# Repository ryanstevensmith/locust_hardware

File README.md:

# Locust Hardware

Open hardware for **Locust**, a low-cost acoustic monitoring sensor developed with Imperial College London. It records audio to a microSD card in the field and can optionally send data over NB-IoT through a plug-in daughter board.

This repository contains the KiCad design files, manufacturing outputs and a firmware flashing tool for the electronics.

## Boards

| Board | Description | Latest release |
|-------|-------------|----------------|
| [IC_001 - Low Cost Audio Sensor](IC_001%20-%20Low%20Cost%20Audio%20Sensor/) | Main board: ESP32-S3 audio recorder with microSD storage and Li-ion battery management | v3.0 |
| [IC_002 - Acoustic Nb-IoT Daughter Board](IC_002%20-%20Acoustic%20Nb-IoT%20Daughter%20Board/) | Optional NB-IoT add-on board for sending data off the device | v3.0 |

### IC_001 – Low Cost Audio Sensor

- **MCU:** Espressif ESP32-S3-WROOM-1 (N16R8: 16 MB flash, 8 MB PSRAM)
- **Audio chain:** Syntiant SPV0142LR5H analogue MEMS microphone → TI OPA1671 preamp → TI TLV320ADC3101 audio ADC (I2S)
- **Storage:** microSD card
- **Power:** single-cell Li-ion input, TI BQ21080 charger, TI BQ27427 fuel gauge, 2× TI TPS63000 buck-boost regulators, USB-C for charging and programming
- **User interface:** 5 buttons and an addressable RGB LED panel for setting the clock, sample rate (8–96 kHz), duty cycle, gain and recording schedule, plus status LEDs
- **Expansion:** 2× Qwiic/STEMMA QT (JST-SH, I2C) and a 10-way FFC connector (J6) to IC_002

### IC_002 – Acoustic NB-IoT Daughter Board

- **Modem:** Quectel BC65 NB-IoT module
- **SIM:** nano-SIM holder with ESD protection
- **Antenna:** edge-mount SMA or U.FL (fit **one** antenna at a time)
- **Interface:** 10-way FFC connector (J3) to IC_001, with level-shifted UART and modem power/reset control

## Repository layout

Each board follows the same structure:

```
IC_00X - <Board Name>/
  working/                              KiCad project (in-progress design)
  IC_00X - <Board Name> - Release vX.Y/
    ... - Schematics - vX.Y.pdf
    ... - Layer Drawings - vX.Y.pdf
    ... - vX.Y.step                     3D model of the assembled board
    ... - proj files - vX.Y.zip         KiCad project snapshot for this release
    front.png / back.png                Board renders
    manufacturing files/
      BoM / PnP (JLC and EXT)           Bill of materials and pick-and-place files
      <gerber folders and zip>          Gerbers (RS-274X and X2) and drill files
firmware/                               Pre-built test firmware binaries
uploader/                               Windows flashing tool (Python source)
```

**JLC** files are formatted for JLCPCB assembly (LCSC part numbers). **EXT** files are for any other assembler and list manufacturer and Digi-Key part numbers.

Use the **v3.0** releases for new builds. The v1.0 releases are kept for reference.

## Building a unit

A complete unit needs:

| Item | Part |
|------|------|
| Main board | IC_001 v3.0 |
| NB-IoT board (optional) | IC_002 v3.0 |
| Board-to-board cable | Molex 15167-0250 FFC |
| Antenna | KYOCERA AVX 9000440F0-AA12L0150 (U.FL) |
| Battery | 3× 18650 cells in parallel (1S3P), see below |
| Enclosure | Injection-moulded enclosure, not included in this repo |

### Battery

- 1S3P 18650 pack, 4.2 V fully charged, about 9000 mAh
- Connector: Molex PicoBlade housing 51021-0300, mates with J3 on IC_001
  - Pin 1: battery +
  - Pin 2: thermistor, 10 kΩ NTC (optional)
  - Pin 3: battery −

> ⚠️ Check the polarity before connecting. Many off-the-shelf PicoBlade battery leads are wired the other way round.

## Flashing firmware

Pre-built test firmware is in [`firmware/`](firmware/). The firmware source code is not part of this repository.

### Windows (updater tool)

1. Put `updater.exe` in the same folder as `bootloader.bin`, `partitions.bin` and `firmware.bin`.
2. Connect IC_001 to your PC with a USB-C **data** cable.
3. Run `updater.exe`. The tool is unsigned, so if Windows SmartScreen warns you, click **More info → Run anyway**.
4. Select the board's COM port (check Device Manager if you are unsure which one it is) and click **Flash Firmware**.
5. Wait for the success message.

If the board isn't detected, hold **BOOT**, press **RESET**, then release **BOOT** to enter download mode.

### Any platform (esptool)

```bash
pip install esptool
esptool.py --chip esp32s3 --port <PORT> --baud 460800 write_flash -z \
  0x0 bootloader.bin \
  0x8000 partitions.bin \
  0x10000 firmware.bin
```

### Building the updater from source

```bash
cd uploader
pip install -r requirements.txt pyinstaller
pyinstaller updater.spec
```

The executable is written to `uploader/dist/updater.exe`.

## Design tools

- **ECAD:** KiCad. Some parts use a custom `SR_*` library, which is not included. KiCad stores footprints inside the board file and symbols inside the schematic, so the projects open and can be edited without that library. Library paths use the `${SR_KICAD_LIB}` path variable.
- **Gerbers:** provided in both standard RS-274X and Gerber X2 formats

## License

The hardware designs are released under the [CERN Open Hardware Licence Version 2 – Permissive](LICENSE) (CERN-OHL-P-2.0).

The updater software in [`uploader/`](uploader/) is released under the [MIT License](uploader/LICENSE).

Copyright © 2026 Ryan Smith.

## Acknowledgements

Designed by [Smith Robotics](https://smithrobotics.co.uk) for Imperial College London.

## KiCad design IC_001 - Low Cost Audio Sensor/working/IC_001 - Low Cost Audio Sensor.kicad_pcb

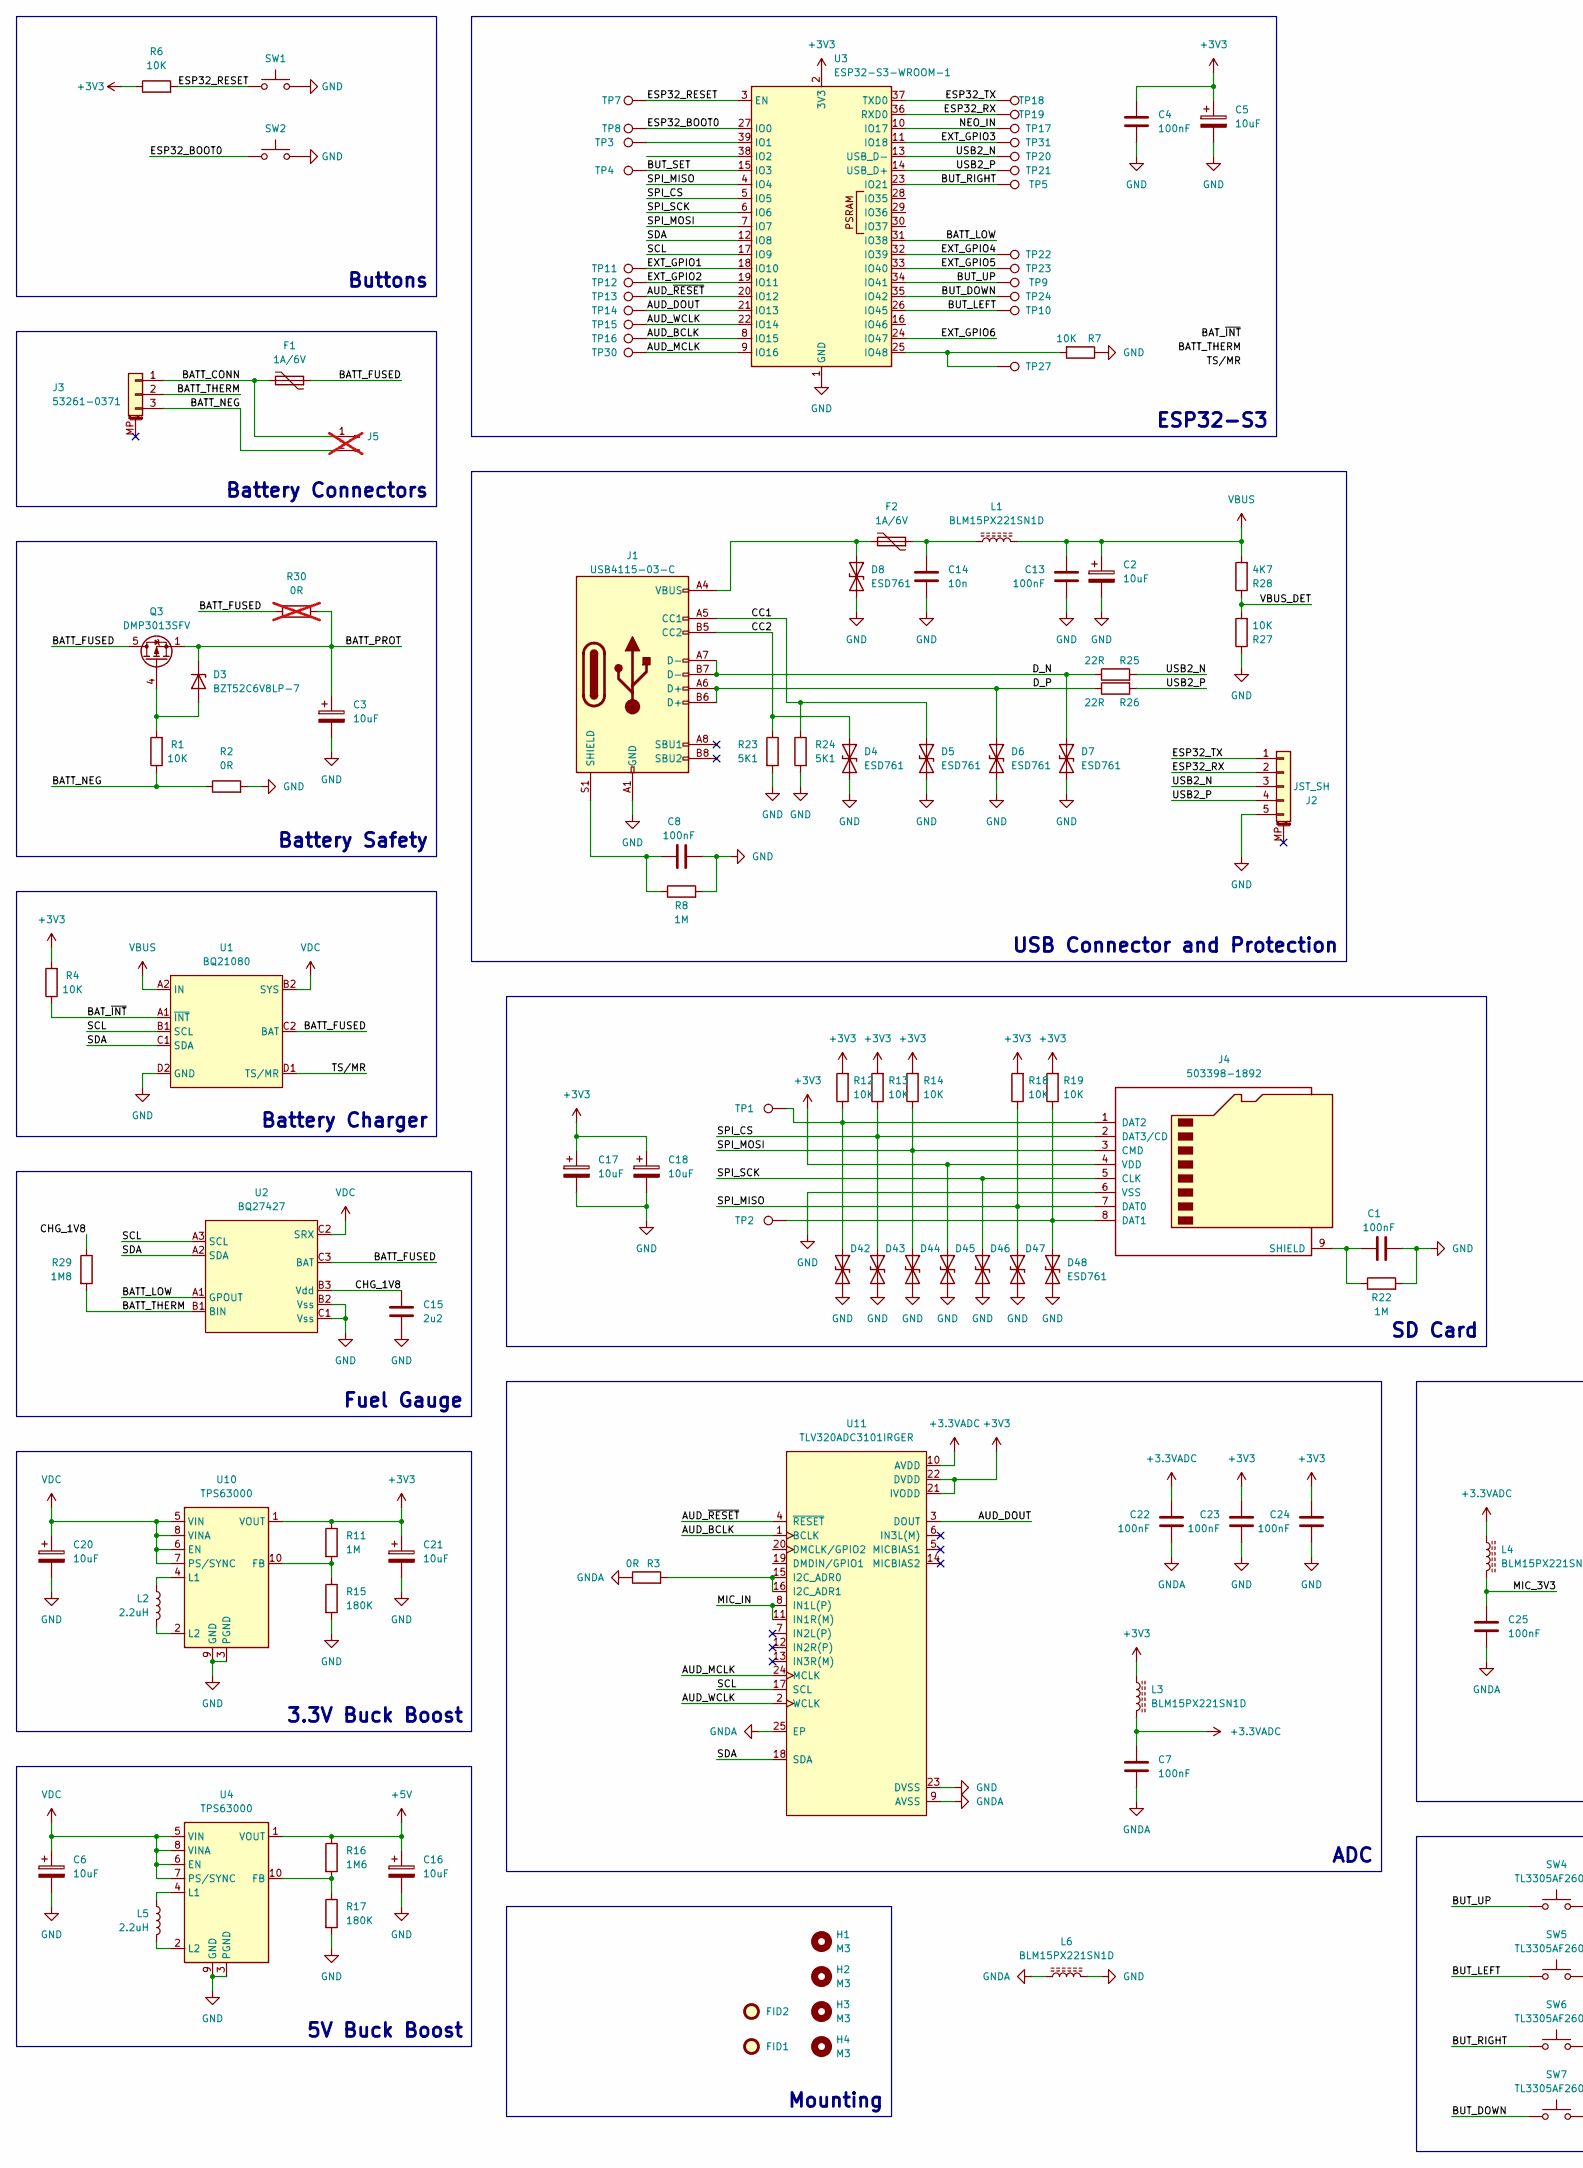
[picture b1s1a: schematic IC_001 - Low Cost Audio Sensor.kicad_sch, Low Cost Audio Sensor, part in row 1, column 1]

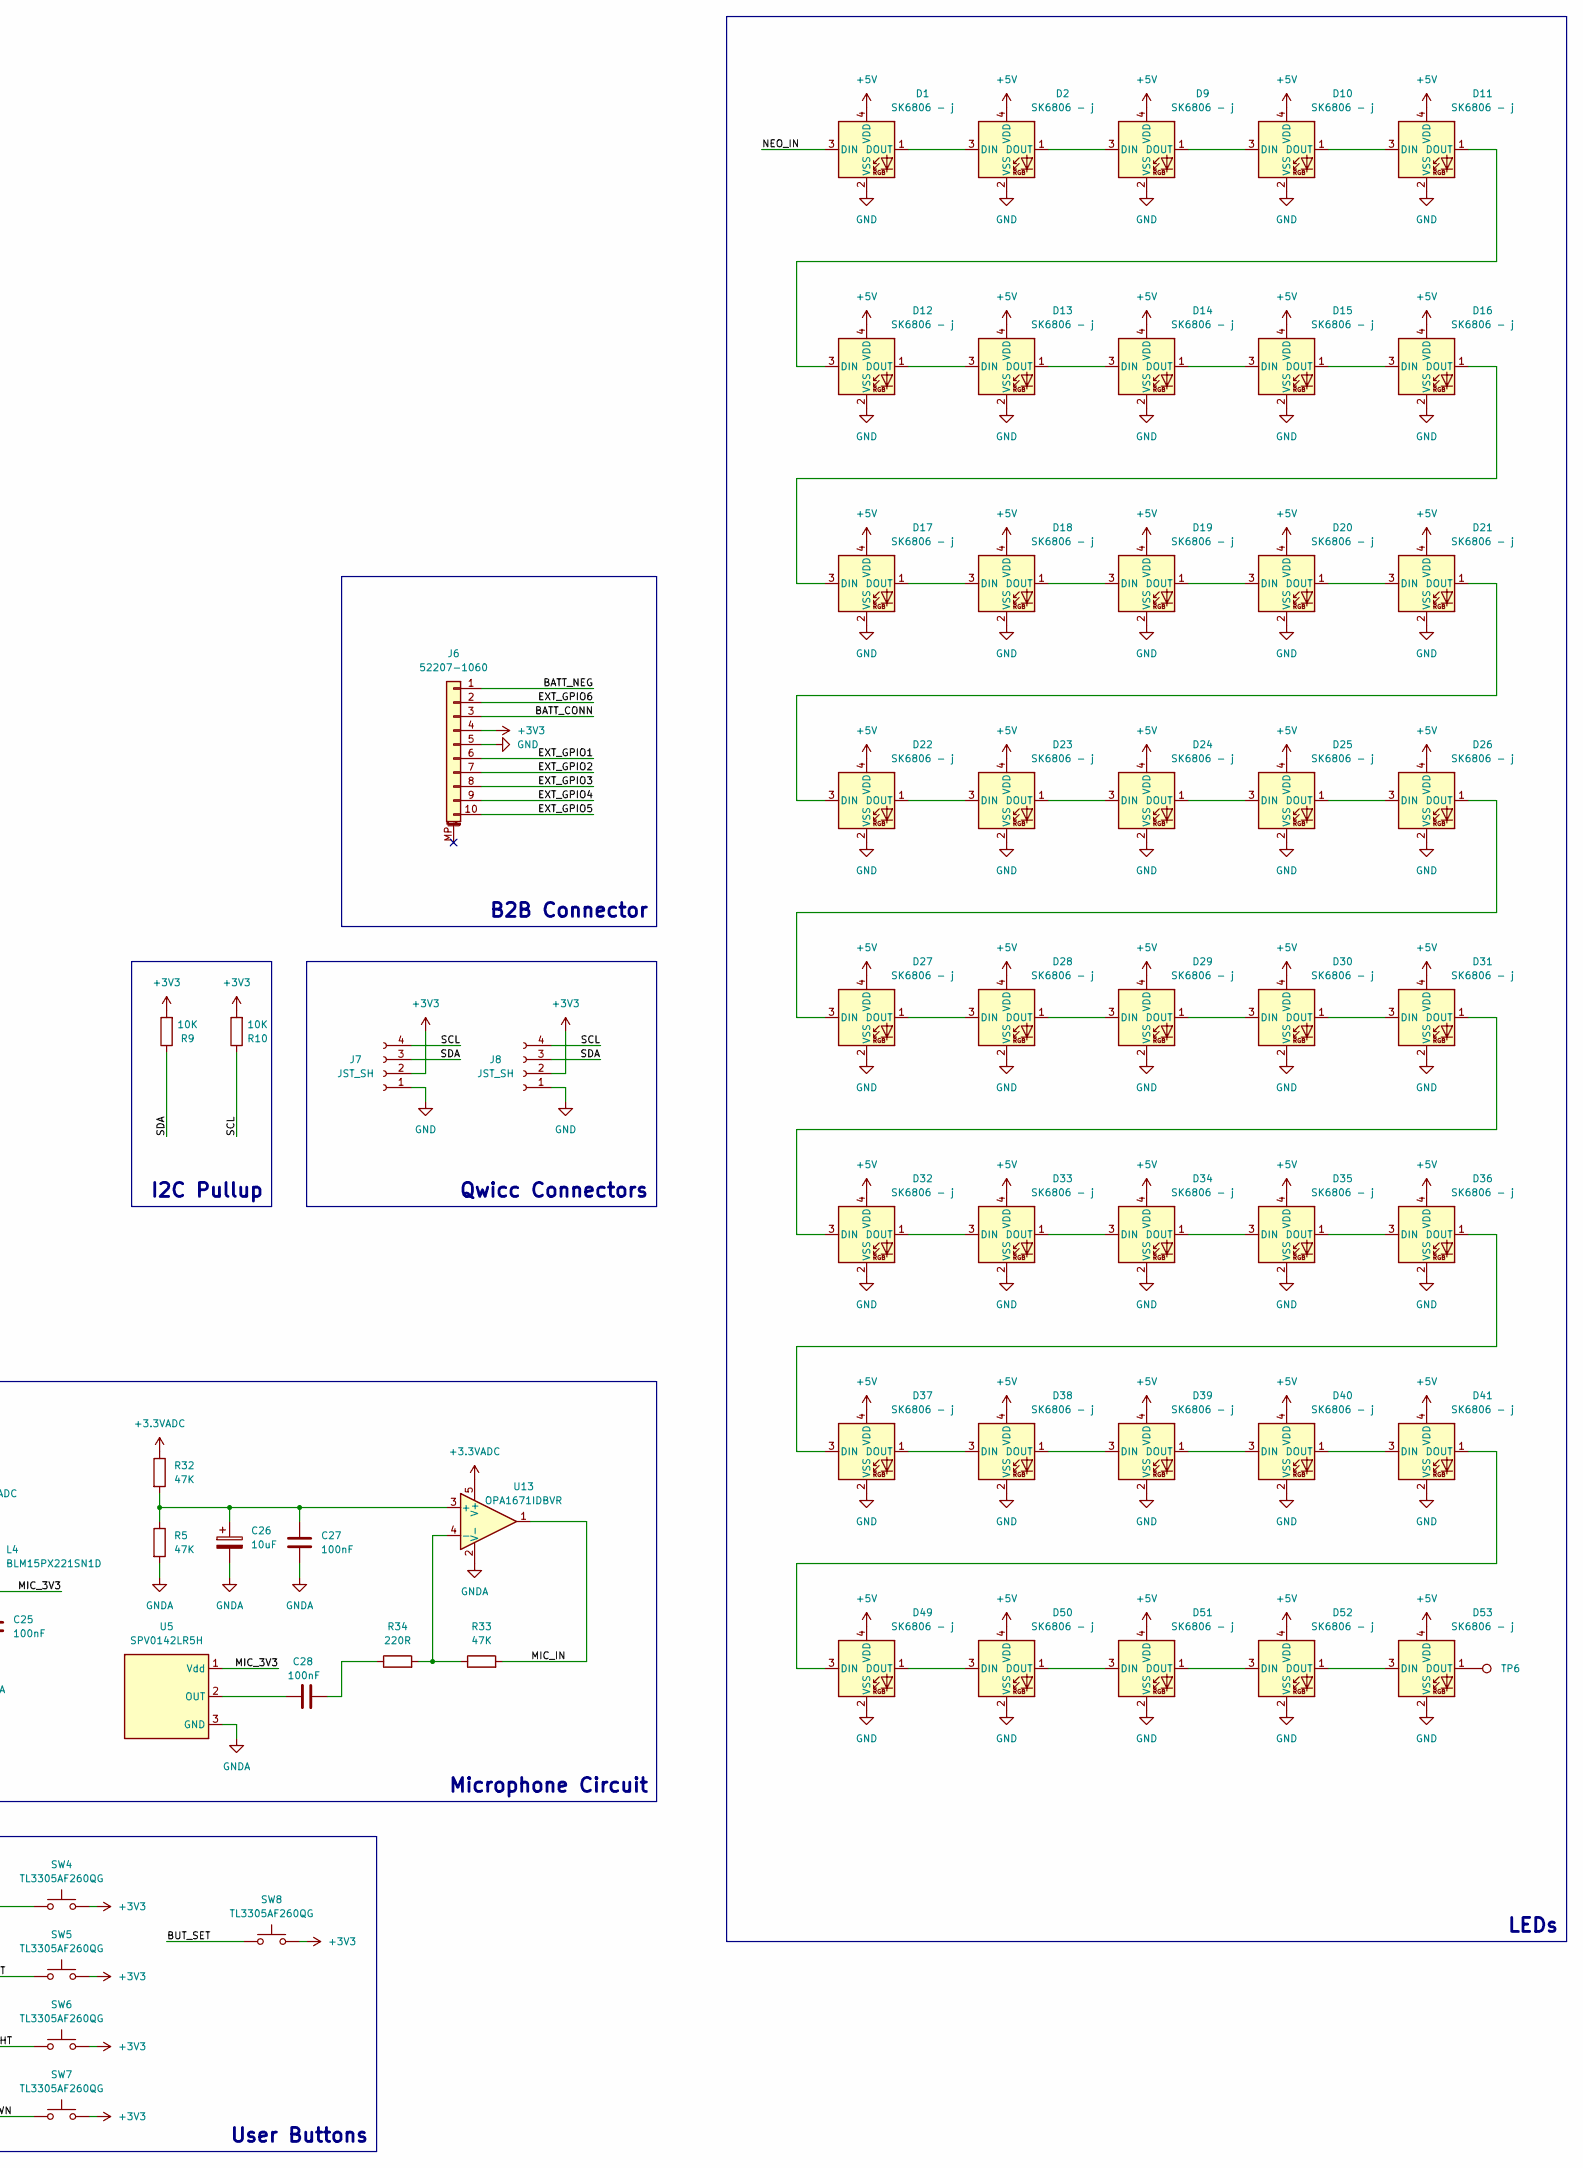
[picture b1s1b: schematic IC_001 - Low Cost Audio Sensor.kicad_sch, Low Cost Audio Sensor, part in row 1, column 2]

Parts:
C1, C4, C7, C8, C13, C22, C23, C24, C25, C27, C28: 100nF; C_0402_1005Metric; Digi-Key 490-6328-2-ND
C2, C3, C5, C6, C16, C17, C18, C20, C21, C26: 10uF; CP_EIA-3216-18_Kemet-A; LCSC C128254
C14: 10n; C_0402_1005Metric; LCSC C1524
C15: 2u2; C_0402_1005Metric; LCSC C193620
D1, D2, D9, D10, D11, D12, D13, D14, D15, D16, D17, D18, D19, D20, D21, D22, D23, D24, D25, D26, D27, D28, D29, D30, D31, D32, D33, D34, D35, D36, D37, D38, D39, D40, D41, D49, D50, D51, D52, D53: SK6806 - j; LED_SK6805_PLCC4_2.4x2.7mm_P1.3mm; LCSC C2909056
D3: BZT52C6V8LP-7; X1-DFN1006-2; LCSC C460796
D4, D5, D6, D7, D8, D42, D43, D44, D45, D46, D47, D48: ESD761; Texas_DPY0002A_0.6x1mm_P0.65mm; LCSC C20345399
F1, F2: 1A/6V; Fuse_0603_1608Metric; LCSC C516069
FID1, FID2: Fiducial; Fiducial_1mm_Mask2mm
H1, H2, H3, H4: M3; MountingHole_3.2mm_M3
J1: USB4115-03-C; USB_C_Receptacle_GCT_USB4115-03-C; LCSC C5250720
J2: JST_SH; JST_SH_BM05B-SRSS-TB_1x05-1MP_P1.00mm_Vertical; LCSC C160391
J3: 53261-0371; Molex_PicoBlade_53261-0371_1x03-1MP_P1.25mm_Horizontal; LCSC C293630
J4: 503398-1892; LCSC C428492
J5: Conn_01x02_Pin; PinHeader_1x02_P2.54mm_Horizontal; not fitted
J6: 52207-1060; LCSC C3168739
J7, J8: JST_SH; JST_SH_SM04B-SRSS-TB_1x04-1MP_P1.00mm_Horizontal; LCSC C160404
L1, L3, L4, L6: BLM15PX221SN1D; L_0402_1005Metric; LCSC C160973
L2, L5: 2.2uH; L_Bourns-SRN4018; LCSC C135262
Q3: DMP3013SFV; Diodes_PowerDI3333-8; LCSC C264098
R1, R4, R6, R7, R9, R10, R12, R13, R14, R18, R19, R27: 10K; R_0402_1005Metric; Digi-Key 541-10.0KLTR-ND
R2, R3: 0R; R_0402_1005Metric; LCSC C17168
R5, R32, R33: 47K; R_0402_1005Metric; LCSC C25792
R8, R11, R22: 1M; R_0402_1005Metric; LCSC C26087
R15, R17: 180K; R_0402_1005Metric; LCSC C25541
R16: 1M6; R_0402_1005Metric; LCSC C57065
R23, R24: 5K1; R_0402_1005Metric; LCSC C25941
R25, R26: 22R; R_0402_1005Metric; LCSC C25152
R28: 4K7; R_0402_1005Metric; LCSC C25900
R29: 1M8; R_0402_1005Metric; LCSC C473021
R30: 0R; R_0402_1005Metric; LCSC C17168; not fitted
R34: 220R; R_0402_1005Metric; LCSC C25151
SW1, SW2: SW_Push; SW_SPST_B3U-1000P; LCSC C231329
SW4, SW5, SW6, SW7, SW8: TL3305AF260QG; SW_SPST_TL3305A; LCSC C2886902
TP1, TP2, TP3, TP4, TP5, TP6, TP7, TP8, TP9, TP10, TP11, TP12, TP13, TP14, TP15, TP16, TP17, TP18, TP19, TP20, TP21, TP22, TP23, TP24, TP27, TP30, TP31: TestPoint; TestPoint_Pad_D1.0mm
U1: BQ21080; Texas_DSBGA-8-1.6mmx1mm_P0.4mm; LCSC C6869615
U2: BQ27427; Texas_DSBGA-9-1.6mmx1.6_P0.5mm; LCSC C6075475
U3: ESP32-S3-WROOM-1; LCSC C2913202
U4, U10: TPS63000; Texas_DRC0010J_ThermalVias; LCSC C24966
U5: SPV0142LR5H; SPV0142LR5H-1; LCSC C45062176
U11: TLV320ADC3101IRGER; QFN-24-1EP_4x4mm_P0.5mm_EP2.8x2.8mm; LCSC C162409
U13: OPA1671IDBVR; TSOT-23-5; LCSC C1849409

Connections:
+3.3VADC: C7.1, C22.1, L3.2, L4.1, R32.1, U11.10 (AVDD), U13.5 (V+)
+3V3: C4.1, C5.1, C17.1, C18.1, C21.1, C23.1, C24.1, D45.1 (A1), J4.4 (VDD), J6.4, J7.2, J8.2, L3.1, R4.2, R6.1, R9.2, R10.2, R11.1, R12.2, R13.2, R14.2, R18.2, R19.2, SW4.2, SW5.2, SW6.2, SW7.2, SW8.2, U3.2 (3V3), U10.1 (VOUT), U11.21 (IVODD), U11.22 (DVDD)
+5V: C16.1, D1.4 (VDD), D2.4 (VDD), D9.4 (VDD), D10.4 (VDD), D11.4 (VDD), D12.4 (VDD), D13.4 (VDD), D14.4 (VDD), D15.4 (VDD), D16.4 (VDD), D17.4 (VDD), D18.4 (VDD), D19.4 (VDD), D20.4 (VDD), D21.4 (VDD), D22.4 (VDD), D23.4 (VDD), D24.4 (VDD), D25.4 (VDD), D26.4 (VDD), D27.4 (VDD), D28.4 (VDD), D29.4 (VDD), D30.4 (VDD), D31.4 (VDD), D32.4 (VDD), D33.4 (VDD), D34.4 (VDD), D35.4 (VDD), D36.4 (VDD), D37.4 (VDD), D38.4 (VDD), D39.4 (VDD), D40.4 (VDD), D41.4 (VDD), D49.4 (VDD), D50.4 (VDD), D51.4 (VDD), D52.4 (VDD), D53.4 (VDD), R16.1, U4.1 (VOUT)
/AUD_BCLK: TP16.1, U3.8 (IO15), U11.1 (BCLK)
/AUD_DOUT: TP14.1, U3.21 (IO13), U11.3 (DOUT)
/AUD_MCLK: TP30.1, U3.9 (IO16), U11.24 (MCLK)
/AUD_WCLK: TP15.1, U3.22 (IO14), U11.2 (WCLK)
/AUD_~RESET: TP13.1, U3.20 (IO12), U11.4 (~RESET)
/BATT_CONN: F1.2, J3.1, J5.1, J6.3
/BATT_FUSED: F1.1, Q3.5 (D), R30.1, U1.C2 (BAT), U2.C3 (BAT)
/BATT_LOW: U2.A1 (GPOUT), U3.31 (IO38)
/BATT_NEG: J3.3, J5.2, J6.1, R1.1, R2.1
/BATT_PROT: C3.1, D3.1 (K), Q3.1 (S), Q3.2 (S), Q3.3 (S), R30.2
/BATT_THERM: J3.2, R29.2, U2.B1 (BIN)
/BAT_~INT: R4.1, U1.A1 (~INT)
/BUT_DOWN: SW7.1, TP24.1, U3.35 (IO42)
/BUT_LEFT: SW5.1, TP10.1, U3.26 (IO45)
/BUT_RIGHT: SW6.1, TP5.1, U3.23 (IO21)
/BUT_SET: SW8.1, TP4.1, U3.15 (IO3)
/BUT_UP: SW4.1, TP9.1, U3.34 (IO41)
/CC1: D5.1 (A1), J1.A5 (CC1), R24.1
/CC2: D4.1 (A1), J1.B5 (CC2), R23.1
/CHG_1V8: C15.1, R29.1, U2.B3 (Vdd)
/D_N: D7.1 (A1), J1.A7 (D-), J1.B7 (D-), R25.1
/D_P: D6.1 (A1), J1.A6 (D+), J1.B6 (D+), R26.1
/ESP32_BOOT0: SW2.1, TP8.1, U3.27 (IO0)
/ESP32_RESET: R6.2, SW1.1, TP7.1, U3.3 (EN)
/ESP32_RX: J2.2, TP19.1, U3.36 (RXD0)
/ESP32_TX: J2.1, TP18.1, U3.37 (TXD0)
/EXT_GPIO1: J6.6, TP11.1, U3.18 (IO10)
/EXT_GPIO2: J6.7, TP12.1, U3.19 (IO11)
/EXT_GPIO3: J6.8, TP31.1, U3.11 (IO18)
/EXT_GPIO4: J6.9, TP22.1, U3.32 (IO39)
/EXT_GPIO5: J6.10, TP23.1, U3.33 (IO40)
/EXT_GPIO6: J6.2, U3.24 (IO47)
/MIC_3V3: C25.1, L4.2, U5.1 (Vdd)
/MIC_IN: R33.2, U11.8 (IN1L(P)), U11.11 (IN1R(M)), U13.1
/NEO_IN: D1.3 (DIN), TP17.1, U3.10 (IO17)
/SCL: J7.4, J8.4, R10.1, U1.B1 (SCL), U2.A3 (SCL), U3.17 (IO9), U11.17 (SCL)
/SDA: J7.3, J8.3, R9.1, U1.C1 (SDA), U2.A2 (SDA), U3.12 (IO8), U11.18 (SDA)
/SPI_CS: D43.1 (A1), J4.2 (DAT3/CD), R13.1, U3.5 (IO5)
/SPI_MISO: D47.1 (A1), J4.7 (DAT0), R18.1, U3.4 (IO4)
/SPI_MOSI: D44.1 (A1), J4.3 (CMD), R14.1, U3.7 (IO7)
/SPI_SCK: D46.1 (A1), J4.5 (CLK), U3.6 (IO6)
/TS/MR: U1.D1 (TS/MR)
/USB2_N: J2.3, R25.2, TP20.1, U3.13 (USB_D-)
/USB2_P: J2.4, R26.2, TP21.1, U3.14 (USB_D+)
/VBUS_DET: R27.2, R28.1
GND: C1.1, C2.2, C3.2, C4.2, C5.2, C6.2, C8.1, C13.2, C14.2, C15.2, C16.2, C17.2, C18.2, C20.2, C21.2, C23.2, C24.2, D1.2 (VSS), D2.2 (VSS), D4.2 (A2), D5.2 (A2), D6.2 (A2), D7.2 (A2), D8.2 (A2), D9.2 (VSS), D10.2 (VSS), D11.2 (VSS), D12.2 (VSS), D13.2 (VSS), D14.2 (VSS), D15.2 (VSS), D16.2 (VSS), D17.2 (VSS), D18.2 (VSS), D19.2 (VSS), D20.2 (VSS), D21.2 (VSS), D22.2 (VSS), D23.2 (VSS), D24.2 (VSS), D25.2 (VSS), D26.2 (VSS), D27.2 (VSS), D28.2 (VSS), D29.2 (VSS), D30.2 (VSS), D31.2 (VSS), D32.2 (VSS), D33.2 (VSS), D34.2 (VSS), D35.2 (VSS), D36.2 (VSS), D37.2 (VSS), D38.2 (VSS), D39.2 (VSS), D40.2 (VSS), D41.2 (VSS), D42.2 (A2), D43.2 (A2), D44.2 (A2), D45.2 (A2), D46.2 (A2), D47.2 (A2), D48.2 (A2), D49.2 (VSS), D50.2 (VSS), D51.2 (VSS), D52.2 (VSS), D53.2 (VSS), J1.A1 (GND), J1.A12 (GND), J1.B1 (GND), J1.B12 (GND), J2.5, J4.6 (VSS), J6.5, J7.1, J8.1, L6.2, R2.2, R7.1, R8.2, R15.2, R17.2, R22.2, R23.2, R24.2, R27.1, SW1.2, SW2.2, U1.D2 (GND), U2.B2 (Vss), U2.C1 (Vss), U3.1 (GND), U3.40 (GND), U3.41 (GND), U4.3 (PGND), U4.9 (GND), U4.11 (PGND), U10.3 (PGND), U10.9 (GND), U10.11 (PGND), U11.23 (DVSS)
GNDA: C7.2, C22.2, C25.2, C26.2, C27.2, L6.1, R3.1, R5.2, U5.3 (GND), U11.9 (AVSS), U11.25 (EP), U13.2 (V-)
unnamed: C14.1, F2.1, L1.1
unnamed: C28.2, R34.1
unnamed: D1.1 (DOUT), D2.3 (DIN)
unnamed: D2.1 (DOUT), D9.3 (DIN)
unnamed: D3.2 (A), Q3.4 (G), R1.2
unnamed: D8.1 (A1), F2.2, J1.A4 (VBUS), J1.A9 (VBUS), J1.B4 (VBUS), J1.B9 (VBUS)
unnamed: D9.1 (DOUT), D10.3 (DIN)
unnamed: D10.1 (DOUT), D11.3 (DIN)
unnamed: D11.1 (DOUT), D12.3 (DIN)
unnamed: D12.1 (DOUT), D13.3 (DIN)
unnamed: D13.1 (DOUT), D14.3 (DIN)
unnamed: D14.1 (DOUT), D15.3 (DIN)
unnamed: D15.1 (DOUT), D16.3 (DIN)
unnamed: D16.1 (DOUT), D17.3 (DIN)
unnamed: D17.1 (DOUT), D18.3 (DIN)
unnamed: D18.1 (DOUT), D19.3 (DIN)
unnamed: D19.1 (DOUT), D20.3 (DIN)
unnamed: D20.1 (DOUT), D21.3 (DIN)
unnamed: D21.1 (DOUT), D22.3 (DIN)
unnamed: D22.1 (DOUT), D23.3 (DIN)
unnamed: D23.1 (DOUT), D24.3 (DIN)
unnamed: D24.1 (DOUT), D25.3 (DIN)
unnamed: D25.1 (DOUT), D26.3 (DIN)
unnamed: D26.1 (DOUT), D27.3 (DIN)
unnamed: D27.1 (DOUT), D28.3 (DIN)
unnamed: D28.1 (DOUT), D29.3 (DIN)
unnamed: D29.1 (DOUT), D30.3 (DIN)
unnamed: D30.1 (DOUT), D31.3 (DIN)
unnamed: D31.1 (DOUT), D32.3 (DIN)
unnamed: D32.1 (DOUT), D33.3 (DIN)
unnamed: D33.1 (DOUT), D34.3 (DIN)
unnamed: D34.1 (DOUT), D35.3 (DIN)
unnamed: D35.1 (DOUT), D36.3 (DIN)
unnamed: D36.1 (DOUT), D37.3 (DIN)
unnamed: D37.1 (DOUT), D38.3 (DIN)
unnamed: D38.1 (DOUT), D39.3 (DIN)
unnamed: D39.1 (DOUT), D40.3 (DIN)
unnamed: D40.1 (DOUT), D41.3 (DIN)
unnamed: D41.1 (DOUT), D49.3 (DIN)
unnamed: D42.1 (A1), J4.1 (DAT2), R12.1, TP1.1
unnamed: D48.1 (A1), J4.8 (DAT1), R19.1, TP2.1
unnamed: D49.1 (DOUT), D50.3 (DIN)
unnamed: D50.1 (DOUT), D51.3 (DIN)
unnamed: D51.1 (DOUT), D52.3 (DIN)
unnamed: D52.1 (DOUT), D53.3 (DIN)
unnamed: D53.1 (DOUT), TP6.1
unnamed: C8.2, J1.S1 (SHIELD), R8.1
unnamed: C1.2, J4.9 (SHIELD), R22.1
unnamed: TP3.1, U3.39 (IO1)
unnamed: R7.2, TP27.1, U3.25 (IO48)
unnamed: R16.2, R17.1, U4.10 (FB)
unnamed: L5.2, U4.4 (L1)
unnamed: L5.1, U4.2 (L2)
unnamed: C28.1, U5.2 (OUT)
unnamed: R11.2, R15.1, U10.10 (FB)
unnamed: L2.2, U10.4 (L1)
unnamed: L2.1, U10.2 (L2)
unnamed: R3.2, U11.15 (I2C_ADR0), U11.16 (I2C_ADR1)
unnamed: C26.1, C27.1, R5.1, R32.2, U13.3 (+)
unnamed: R33.1, R34.2, U13.4 (-)
VBUS: C2.1, C13.1, L1.2, R28.2, U1.A2 (IN)
VDC: C6.1, C20.1, U1.B2 (SYS), U2.C2 (SRX), U4.5 (VIN), U4.6 (EN), U4.7 (PS/SYNC), U4.8 (VINA), U10.5 (VIN), U10.6 (EN), U10.7 (PS/SYNC), U10.8 (VINA)

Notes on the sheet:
Buttons
Battery Safety
I2C Pullup
Fuel Gauge
LEDs
Qwicc Connectors
5V Buck Boost
SD Card
User Buttons
Microphone Circuit
Mounting
Battery Charger
3.3V Buck Boost
Battery Connectors
USB Connector and Protection
B2B Connector
ADC
ESP32-S3

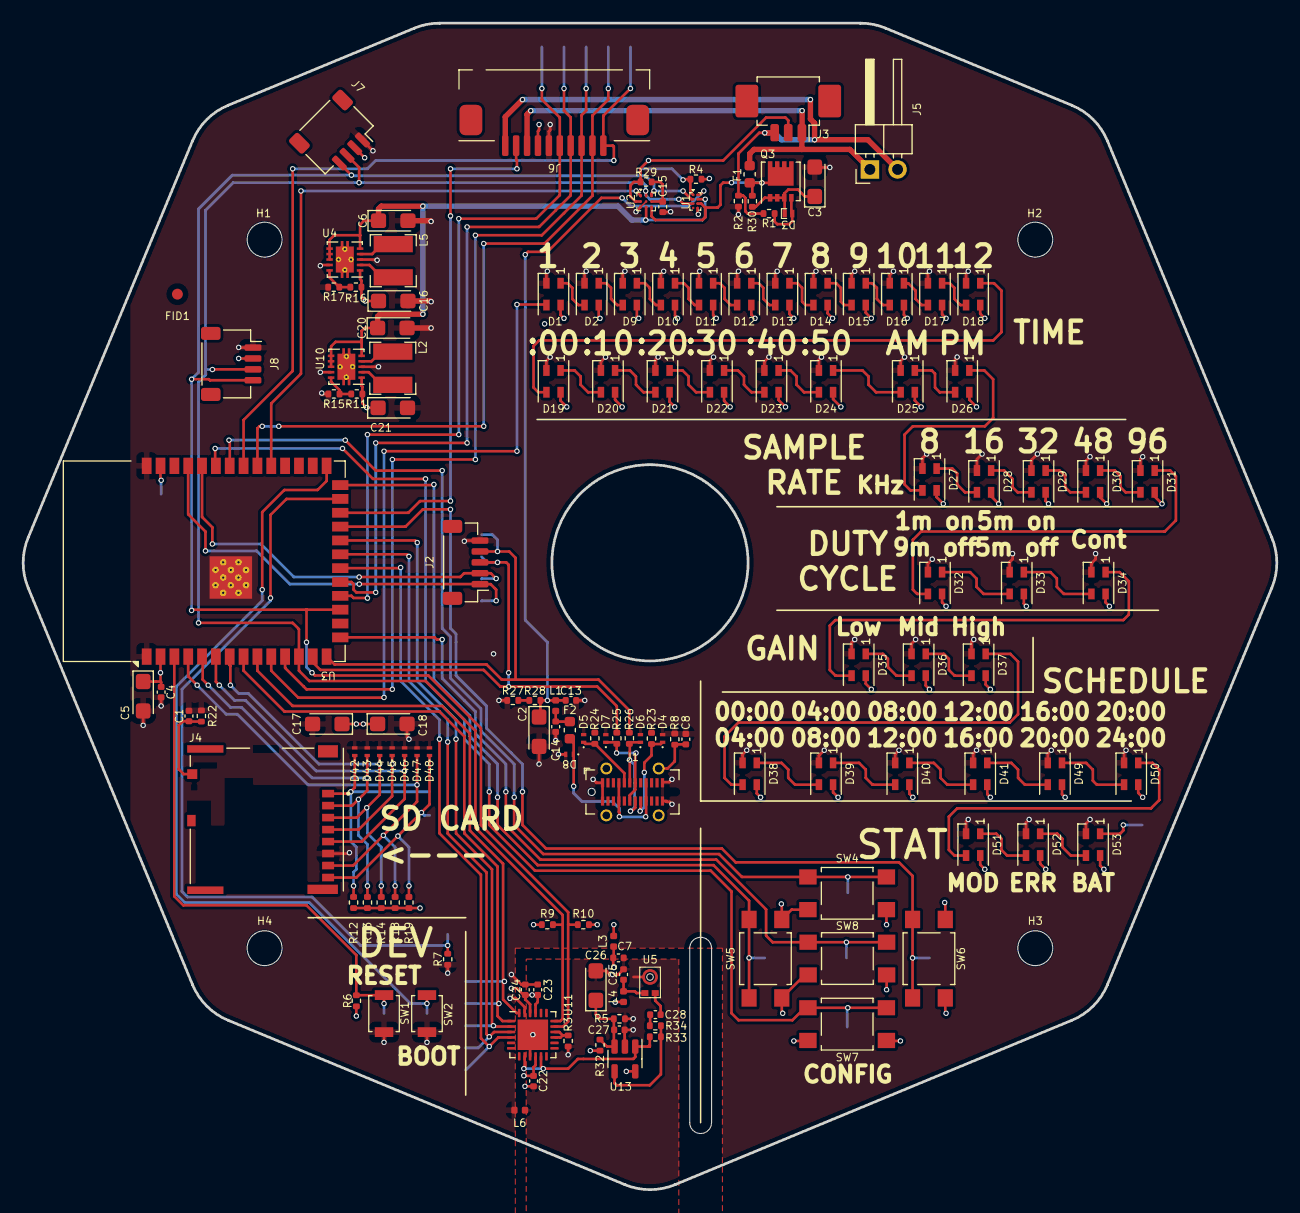
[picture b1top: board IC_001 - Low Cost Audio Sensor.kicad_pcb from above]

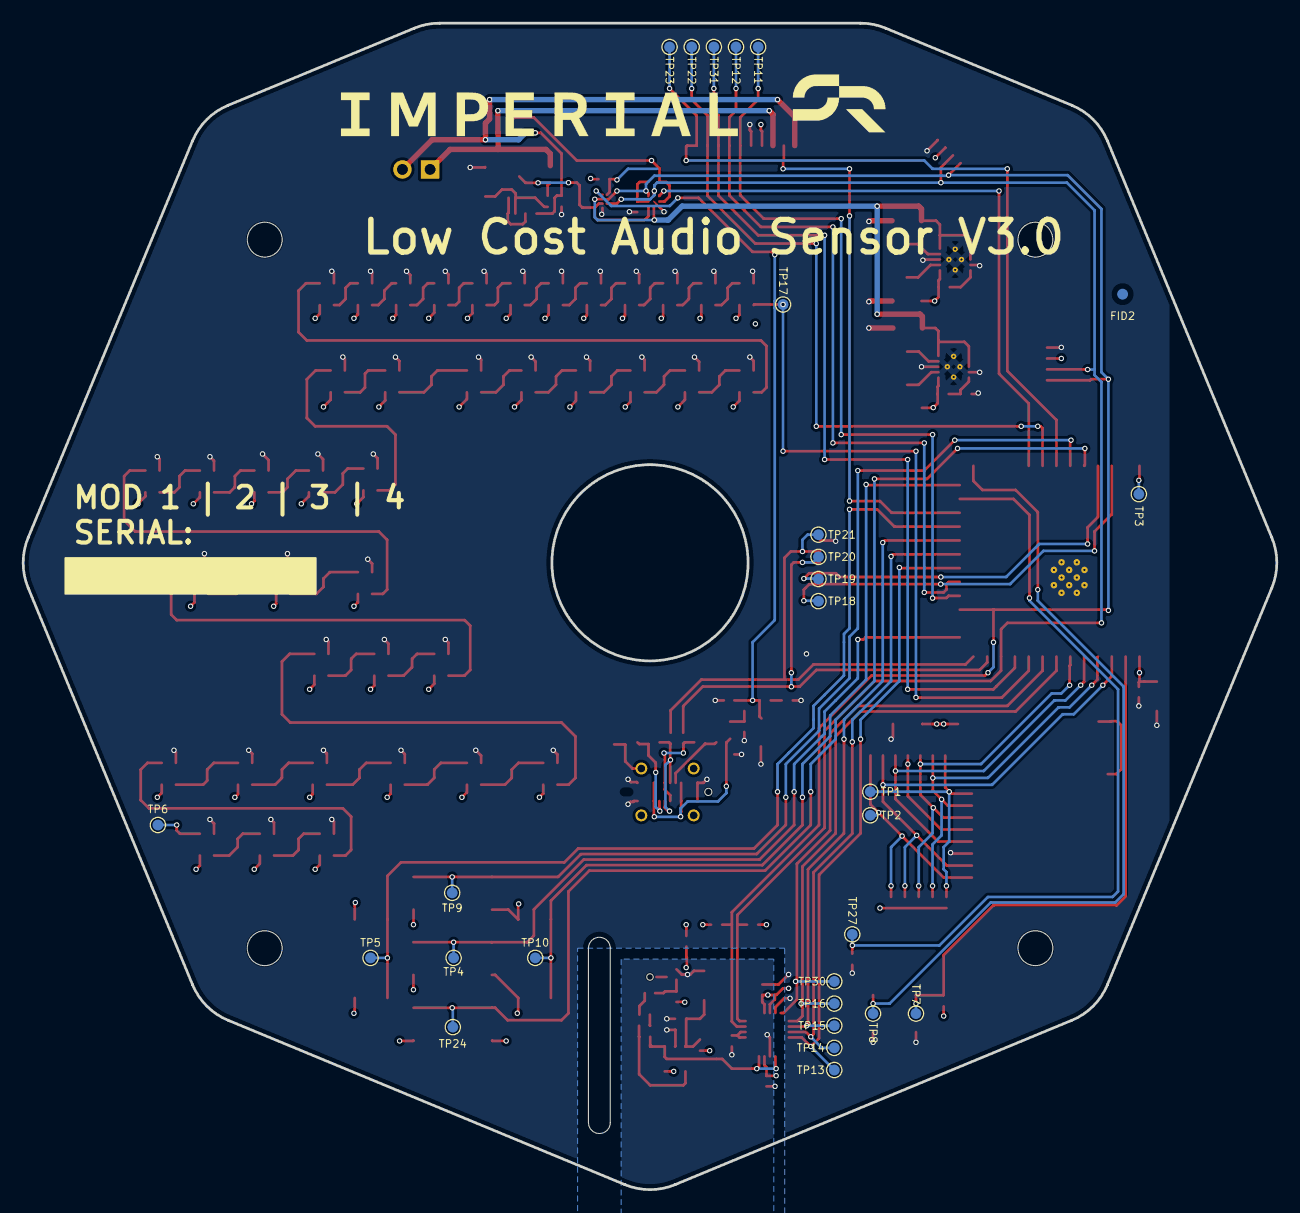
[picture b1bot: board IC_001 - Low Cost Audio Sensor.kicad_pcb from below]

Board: 4 copper layers, 115.0 x 107.0 mm, 172 parts (28 on the bottom side), 111 nets.

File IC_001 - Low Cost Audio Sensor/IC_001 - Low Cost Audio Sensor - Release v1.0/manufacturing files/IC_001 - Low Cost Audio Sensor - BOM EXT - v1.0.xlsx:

Item | Qty | Reference(s) | Value | Footprint | LCSC | PN
1 | 12 | C1, C4, C9, C10, C12, C13, C22, C23, C24, C25, C27, C28 | 100nF | C_0402_1005Metric | C1525 | 885012205037
2 | 10 | C2, C3, C5, C6, C16, C17, C18, C20, C21, C26 | 10uF | CP_EIA-3216-18_Kemet-A | C128254 | T491A106K010AT
3 | 3 | C7, C8, C11 | 1uF | C_0603_1608Metric | C1592 | 885012106030
4 | 1 | C14 | 10n | C_0402_1005Metric | C1524 | 0402B103K500NT
5 | 1 | C15 | 2u2 | C_0402_1005Metric | C193620 | 0402X225K6R3NT
6 | 35 | D1, D2, D9, D10, D11, D12, D13, D14, D15, D16, D17, D18, D19, D20, D21, D22, D2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 | SK6806 - j | LED_SK6805_PLCC4_2.4x2.7mm_P1.3mm | C2922787 | SK6812MINI-HS
7 | 1 | D3 | BZT52C6V8LP-7 | X1-DFN1006-2 | C460796 | BZT52C6V8LP-7
8 | 12 | D4, D5, D6, D7, D8, D42, D43, D44, D45, D46, D47, D48 | ESD761 | Texas_DPY0002A_0.6x1mm_P0.65mm | C20345399 | ESD761DPYR
9 | 2 | F1, F2 | 1A/6V | Fuse_0603_1608Metric | C516069 | JK-SMD0603-100L
10 | 1 | J1 | TYPE-C-31-M-12 | HRO_TYPE-C-31-M-12 | C165948 | TYPE-C-31-M-12
11 | 1 | J2 | JST_SH | JST_SH_BM05B-SRSS-TB_1x05-1MP_P1.00mm_Vertical | C160391 | BM05B-SRSS-TB
12 | 1 | J3 | 53261-0371 | Molex_PicoBlade_53261-0371_1x03-1MP_P1.25mm_Horizontal | C293630 | 532610371
13 | 1 | J4 | 503398-1892 | 503398-1892 | C428492 | 503398-1892
14 | 1 | J6 | 52207-1060 | 52207-1060 | C3168739 | 52207-1060
15 | 2 | J7, J8 | JST_SH | JST_SH_SM04B-SRSS-TB_1x04-1MP_P1.00mm_Horizontal | C160404 | SM04B-SRSS-TB
16 | 2 | L1, L4 | BLM15PX221SN1D | L_0402_1005Metric | C160973 | BLM15PX221SN1D
17 | 2 | L2, L5 | 2.2uH | L_Bourns-SRN4018 | C135262 | SMNR4020-2.2UH
18 | 1 | Q1 | FDC6333C | TSOT-23-6 | C5182070 | FDC6333C
19 | 1 | Q2 | MMDT3904 | SOT-363_SC-70-6 | C3018510 | MMDT3904-7-F
20 | 1 | Q3 | DMP3013SFV | Diodes_PowerDI3333-8 | C264098 | DMP3013SFV-7
21 | 11 | R1, R4, R6, R7, R8, R9, R10, R18, R19, R20, R27 | 10K | R_0402_1005Metric | C25744 | CRCW040210K0FKEDC
22 | 2 | R2, R3 | 0R | R_0402_1005Metric | C17168 | 0402WGF0000TCE
23 | 3 | R5, R32, R33 | 47K | R_0402_1005Metric | C25792 | 0402WGF4702TCE
24 | 2 | R11, R22 | 1M | R_0402_1005Metric | C26087 | 0402WGJ0105TCE
25 | 1 | R12 | 100R | R_0402_1005Metric | C25076 | CRCW0402100RFKEE
26 | 2 | R13, R14 | 100K | R_0402_1005Metric | C25741 | CRCW0402100KFKEE
27 | 2 | R15, R17 | 180K | R_0402_1005Metric | C25541 | 0402WGJ0184TCE
28 | 1 | R16 | 1M6 | R_0402_1005Metric | C57065 | 0402WGJ0165TCE
29 | 2 | R21, R28 | 4K7 | R_0402_1005Metric | C25900 | CRCW04024K70FKEDC
30 | 2 | R23, R24 | 5K1 | R_0402_1005Metric | C25941 | 0402WGJ0512TCE
31 | 2 | R25, R26 | 22R | R_0402_1005Metric | C25152 | 0402WGJ0220TCE
32 | 1 | R29 | 1M8 | R_0402_1005Metric | C473021 | 0402WGJ0185TCE
33 | 1 | R34 | 220R | R_0402_1005Metric | C25151 | 0402WGJ0221TCE
34 | 3 | SW1, SW2, SW3 | SW_Push | SW_SPST_B3U-1000P | C231329 | B3U-1000P
35 | 5 | SW4, SW5, SW6, SW7, SW8 | TL3305AF260QG | SW_SPST_TL3305A | C2886902 | TL3305AF260QG
36 | 1 | U1 | BQ21080 | Texas_DSBGA-8-1.6mmx1mm_P0.4mm | C6869615 | BQ21080YBGR
37 | 1 | U2 | BQ27427 | Texas_DSBGA-9-1.6mmx1.6_P0.5mm | C6075475 | BQ27427YZFR
38 | 1 | U3 | ESP32-S3-MINI-1-N8 | ESP32-S3-MINI-1-N8 | C2913206 | ESP32-S3-MINI-1-N8
39 | 2 | U4, U10 | TPS63000 | Texas_DRC0010J_ThermalVias | C24966 | TPS63000DRCR
40 | 1 | U5 | CH343P | TQFN-16-1EP_3x3mm_P0.5mm_EP1.6x1.6mm | C2846043 | CH343P
41 | 1 | U11 | TLV320ADC3101IRGER | QFN-24-1EP_4x4mm_P0.5mm_EP2.8x2.8mm | C162409 | TLV320ADC3101IRGER
42 | 1 | U12 | SPU0410LR5H-QB | SPU0410LR5H-QB | C2918083 | SPU0410LR5H-QB
43 | 1 | U13 | OPA1671IDBVR | TSOT-23-5 | C1849409 | OPA1671IDBVR
